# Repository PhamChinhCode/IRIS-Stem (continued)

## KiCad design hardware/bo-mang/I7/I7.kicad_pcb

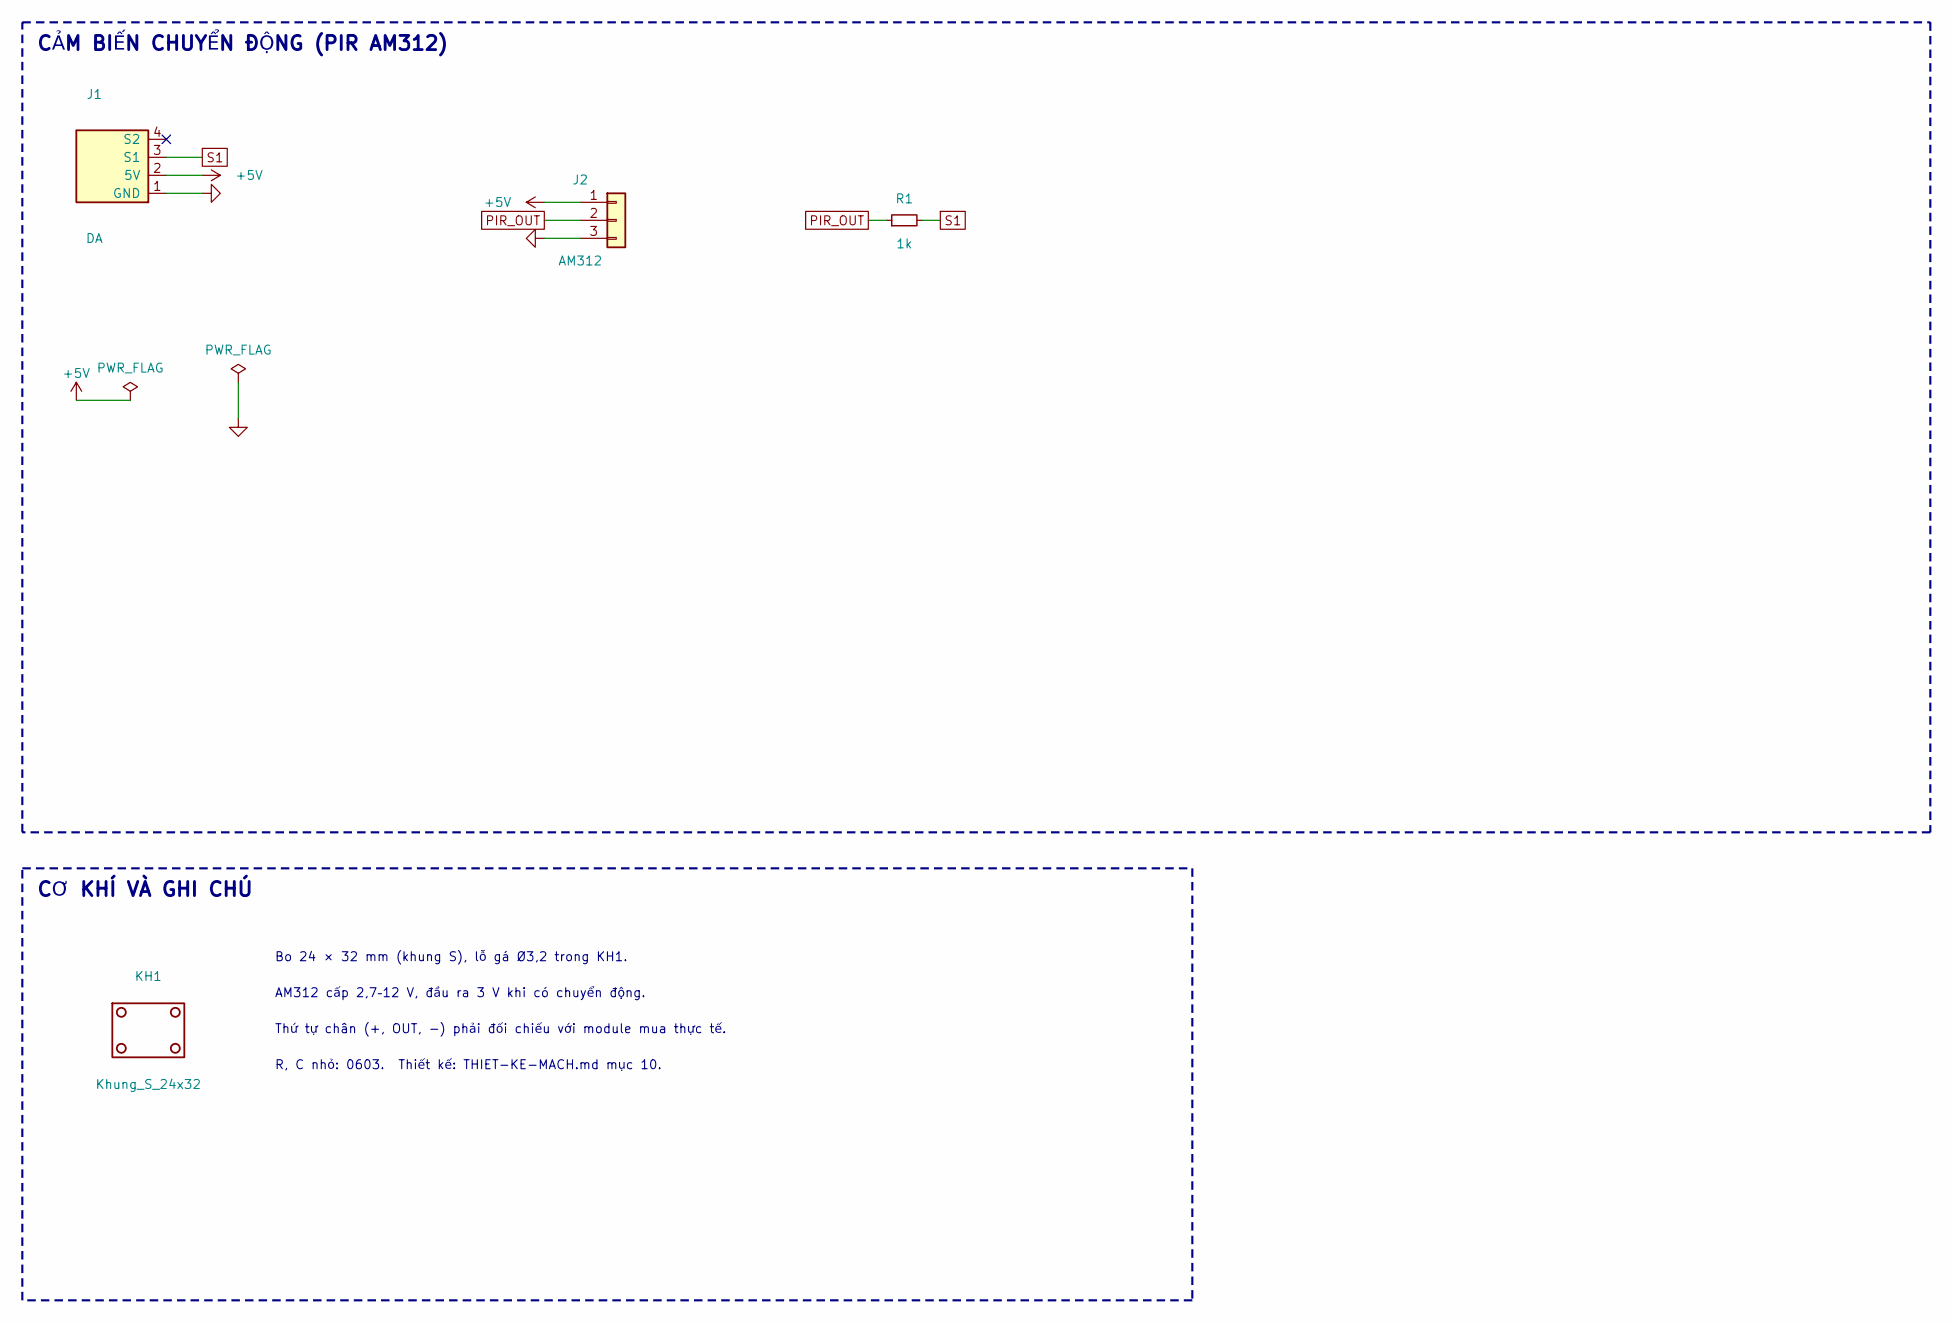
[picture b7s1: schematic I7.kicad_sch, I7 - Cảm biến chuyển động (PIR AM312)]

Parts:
J1: DA; Cong_PH_4P_Ngang
J2: AM312; PinSocket_1x03_P2.54mm_Vertical
KH1: Khung_S_24x32
R1: 1k; R_0603_1608Metric

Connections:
+5V: J1.2 (5V), J2.1
GND: J1.1 (GND), J2.3
PIR_OUT: J2.2, R1.1
S1: J1.3 (S1), R1.2

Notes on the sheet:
CẢM BIẾN CHUYỂN ĐỘNG (PIR AM312)
CƠ KHÍ VÀ GHI CHÚ
Bo 24 × 32 mm (khung S), lỗ gá Ø3,2 trong KH1.
AM312 cấp 2,7–12 V, đầu ra 3 V khi có chuyển động.
Thứ tự chân (+, OUT, −) phải đối chiếu với module mua thực tế.
R, C nhỏ: 0603. Thiết kế: THIET-KE-MACH.md mục 10.

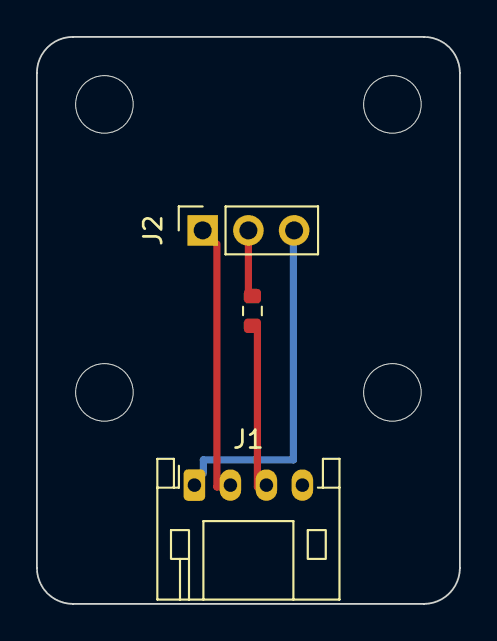
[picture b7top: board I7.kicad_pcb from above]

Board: 2 copper layers, 23.5 x 31.5 mm, 4 parts (0 on the bottom side), 4 nets.

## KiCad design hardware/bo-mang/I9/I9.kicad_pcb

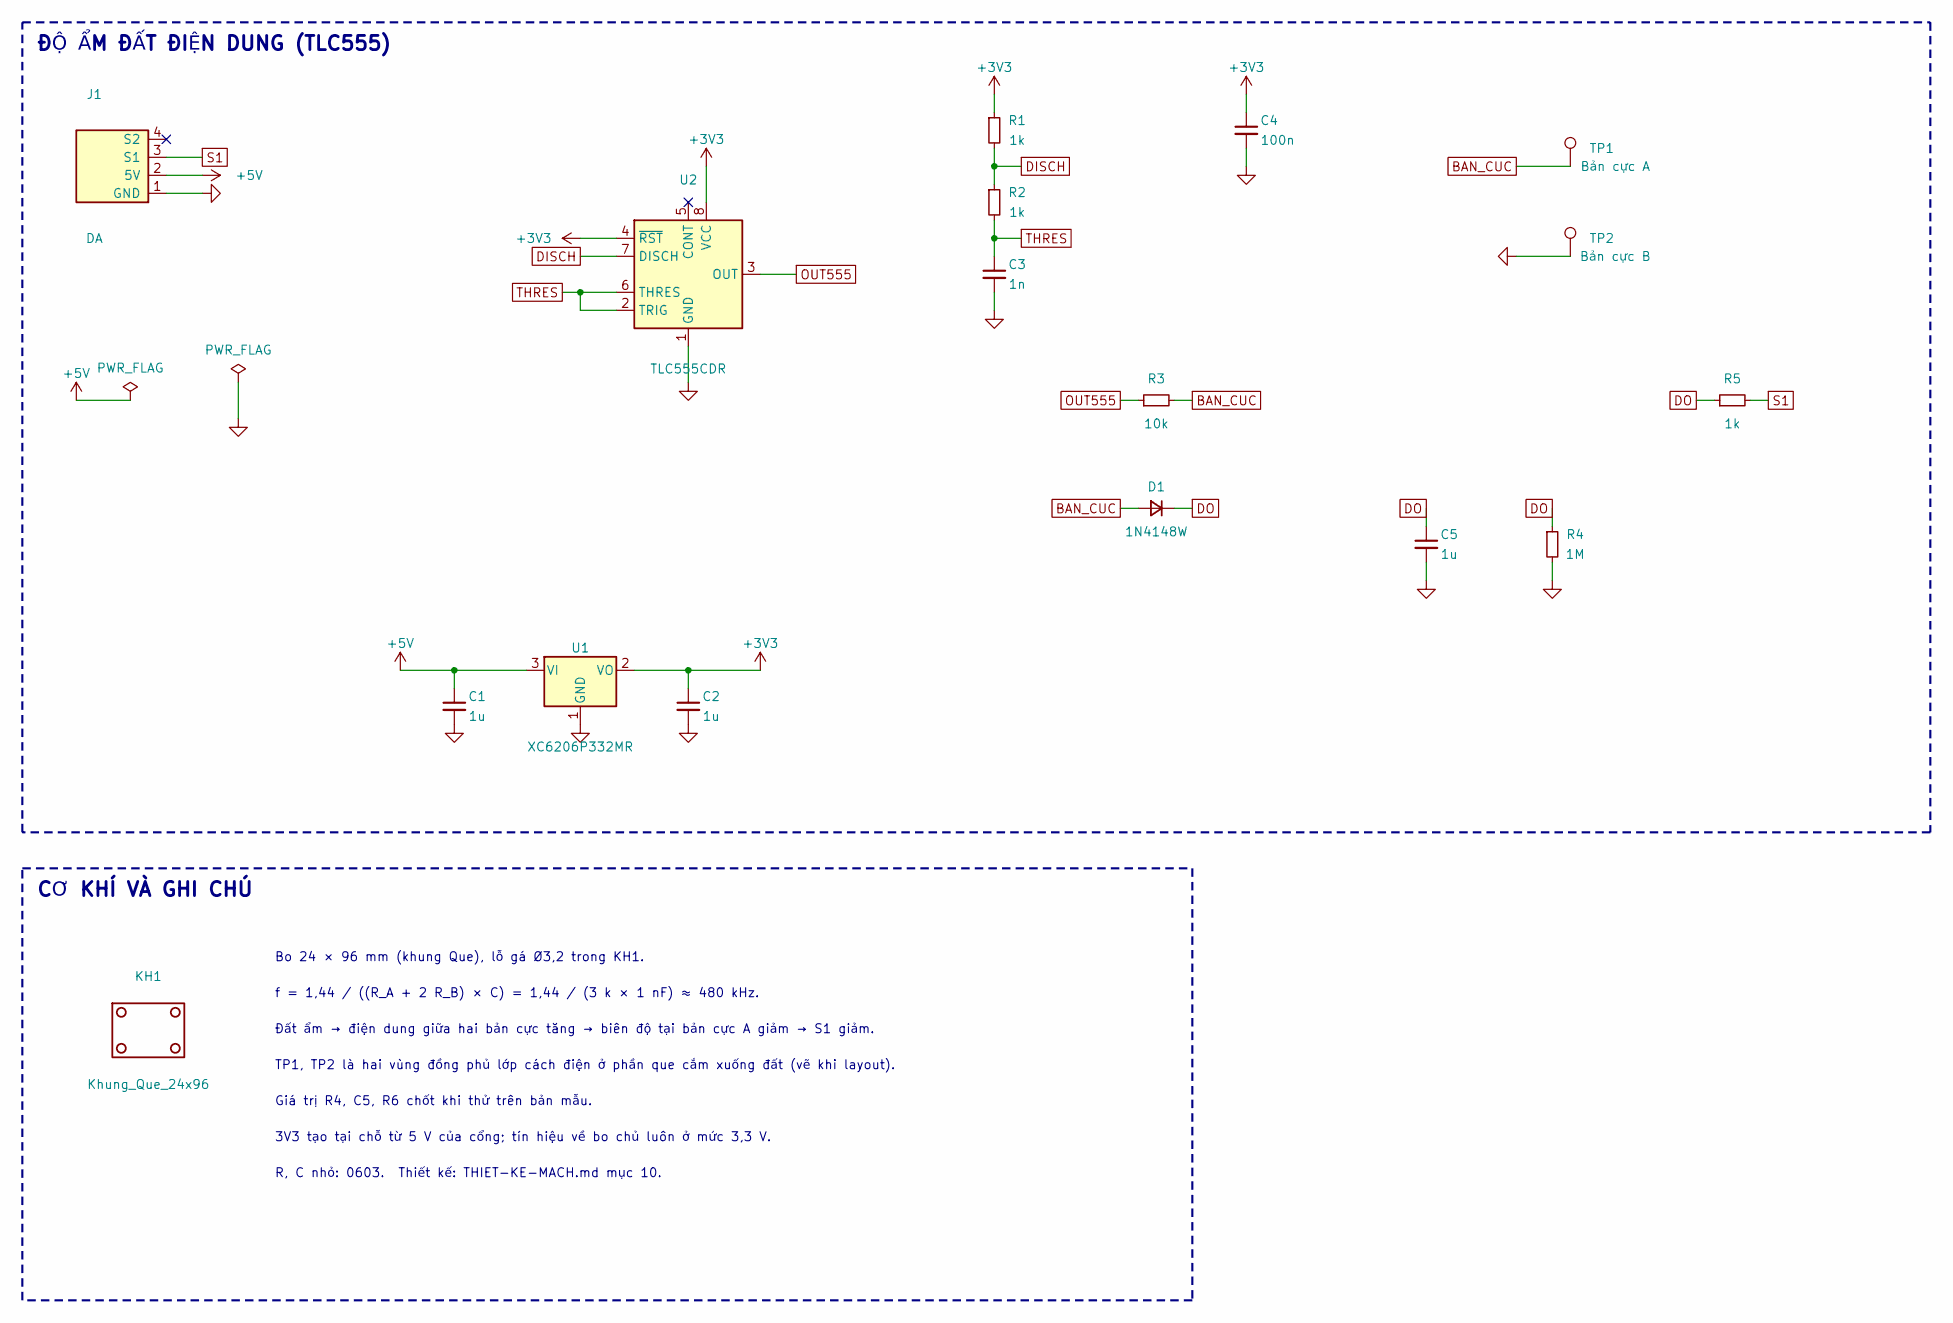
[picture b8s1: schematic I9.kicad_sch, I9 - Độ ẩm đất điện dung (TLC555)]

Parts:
C1, C2, C5: 1u; C_0603_1608Metric
C3: 1n; C_0603_1608Metric
C4: 100n; C_0603_1608Metric
D1: 1N4148W; D_SOD-123
J1: DA; Cong_PH_4P_Ngang
KH1: Khung_Que_24x96
R1, R2, R5: 1k; R_0603_1608Metric
R3: 10k; R_0603_1608Metric
R4: 1M; R_0603_1608Metric
TP1: Bản cực A; TestPoint_Pad_D1.5mm
TP2: Bản cực B; TestPoint_Pad_D1.5mm
U1: XC6206P332MR; SOT-23-3; MPN XC6206P332MR
U2: TLC555CDR; SOIC-8_3.9x4.9mm_P1.27mm; MPN TLC555CDR

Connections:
+3V3: C2.1, C4.1, R1.1, U1.2 (VO), U2.4 (~RST), U2.8 (VCC)
+5V: C1.1, J1.2 (5V), U1.3 (VI)
BAN_CUC: D1.2 (A), R3.2, TP1.1
DISCH: R1.2, R2.1, U2.7 (DISCH)
DO: C5.1, D1.1 (K), R4.1, R5.1
GND: C1.2, C2.2, C3.2, C4.2, C5.2, J1.1 (GND), R4.2, TP2.1, U1.1 (GND), U2.1 (GND)
OUT555: R3.1, U2.3 (OUT)
S1: J1.3 (S1), R5.2
THRES: C3.1, R2.2, U2.2 (TRIG), U2.6 (THRES)

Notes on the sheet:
ĐỘ ẨM ĐẤT ĐIỆN DUNG (TLC555)
CƠ KHÍ VÀ GHI CHÚ
Bo 24 × 96 mm (khung Que), lỗ gá Ø3,2 trong KH1.
f = 1,44 / ((R_A + 2 R_B) × C) = 1,44 / (3 k × 1 nF) ≈ 480 kHz.
Đất ẩm → điện dung giữa hai bản cực tăng → biên độ tại bản cực A giảm → S1 giảm.
TP1, TP2 là hai vùng đồng phủ lớp cách điện ở phần que cắm xuống đất (vẽ khi layout).
Giá trị R4, C5, R6 chốt khi thử trên bản mẫu.
3V3 tạo tại chỗ từ 5 V của cổng; tín hiệu về bo chủ luôn ở mức 3,3 V.
R, C nhỏ: 0603. Thiết kế: THIET-KE-MACH.md mục 10.

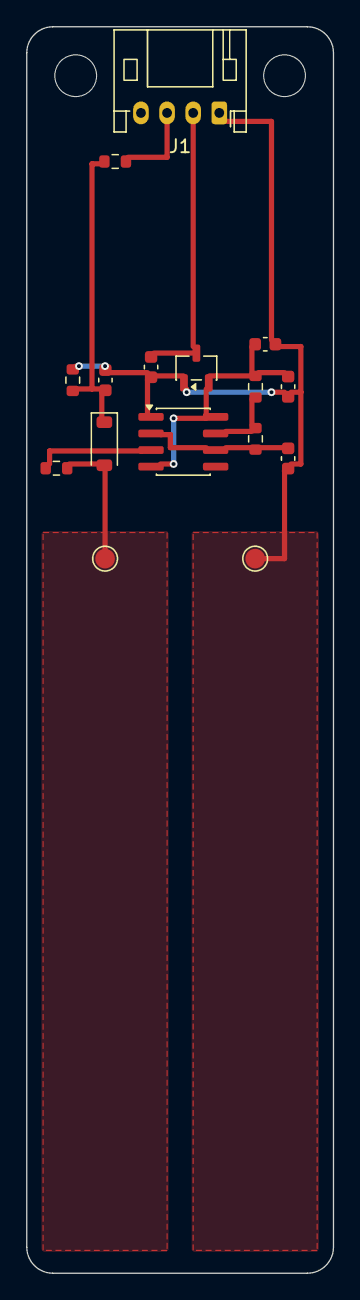
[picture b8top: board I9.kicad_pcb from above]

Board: 2 copper layers, 23.5 x 95.5 mm, 17 parts (0 on the bottom side), 9 nets.
